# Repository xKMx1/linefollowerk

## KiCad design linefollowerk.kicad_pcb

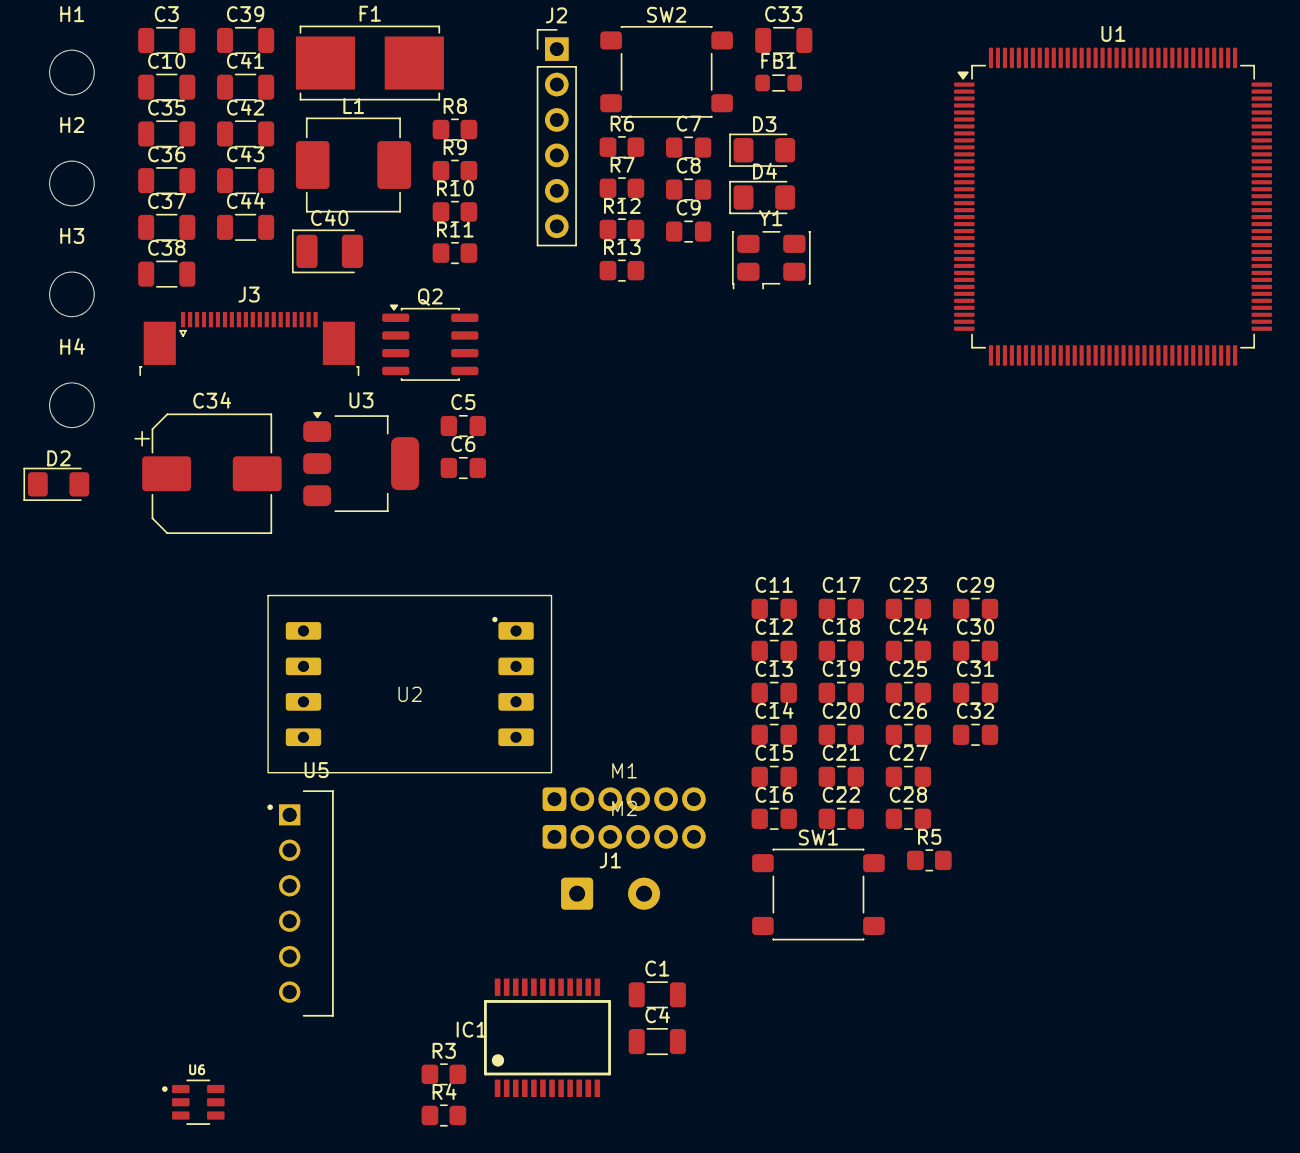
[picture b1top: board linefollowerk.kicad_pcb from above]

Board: 2 copper layers, 79 parts (0 on the bottom side), 57 nets, no tracks yet.

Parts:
C1, C4, C33, C37, C44: 100nF; C_1206_3216Metric
C3, C10, C35, C36, C39, C42, C43: 10uF; C_1206_3216Metric
C5, C23: 10uF; C_0805_2012Metric_Pad1.18x1.45mm_HandSolder
C6, C9, C11, C12, C13, C14, C15, C16, C17, C18, C19, C20, C21, C22, C24, C25, C29, C30: 100nF; C_0805_2012Metric_Pad1.18x1.45mm_HandSolder
C7, C8: 10pF; C_0805_2012Metric_Pad1.18x1.45mm_HandSolder
C26, C28: 1uF; C_0805_2012Metric_Pad1.18x1.45mm_HandSolder
C27: 10nF; C_0805_2012Metric_Pad1.18x1.45mm_HandSolder
C31, C32: 2.2uF; C_0805_2012Metric_Pad1.18x1.45mm_HandSolder
C34: 470uF; CP_Elec_8x10
C38, C41: 22uF; C_1206_3216Metric
C40: 22uF; CP_EIA-3528-21_Kemet-B_HandSolder
D2, D4: RED; LED_1206_3216Metric_Pad1.42x1.75mm_HandSolder
D3: GREEN; LED_1206_3216Metric_Pad1.42x1.75mm_HandSolder
F1: Fuse; Fuseholder_Littelfuse_Nano2_154x
FB1: 220Ω@100MHz; L_0805_2012Metric_Pad1.05x1.20mm_HandSolder
H1, H2, H3, H4: MountingHole; MountingHole_3.2mm_M3
IC1: TB6612FNG; SSOP24
J1: Conn_01x02_Pin; SolderWire-0.5sqmm_1x02_P4.8mm_D0.9mm_OD2.3mm
J2: SWD Connector; PinHeader_1x06_P2.54mm_Vertical
J3: FFC 20p; TE_2-1734839-0_1x20-1MP_P0.5mm_Horizontal
L1: 3.3uH; L_Vishay_IHLP-2525
M1, M2: POLOLU_ENCODER_FOOTPRINT
Q2: AO4407A; SOIC-8_3.9x4.9mm_P1.27mm
R3, R5, R9, R11: 10k; R_0805_2012Metric_Pad1.20x1.40mm_HandSolder
R4, R12, R13: 1k; R_0805_2012Metric_Pad1.20x1.40mm_HandSolder
R6, R10: 100k; R_0805_2012Metric_Pad1.20x1.40mm_HandSolder
R7: 47k; R_0805_2012Metric_Pad1.20x1.40mm_HandSolder
R8: 54.9k; R_0805_2012Metric_Pad1.20x1.40mm_HandSolder
SW1: PTS645; SW_SPST_PTS645Sx43SMTR92
SW2: SW_Push; SW_SPST_PTS645Sx43SMTR92
U1: STM32H743ZIT6; LQFP-144_20x20mm_P0.5mm
U2: MPU_6050
U3: AMS1117-3.3; SOT-223-3_TabPin2
U5: HC-06; MODULE_ZC142200
U6: TPS563201DDCR; SOT95P280X110-6N
Y1: Crystal_GND24; Crystal_SMD_5032-4Pin_5.0x3.2mm

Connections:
+3V3: C3.1, C4.1, C5.1, C6.1, C11.2, C12.2, C13.2, C14.2, C15.2, C16.2, C17.2, C18.2, C19.2, C20.2, C21.2, C22.2, C23.2, C24.2, C25.2, C28.2, C40.1, FB1.2, IC1.20 (VCC), J2.1, J3.1, M1.4 (VCC), M2.4 (VCC), R4.1, U1.6 (VBAT), U1.17 (VDD), U1.30 (VDD), U1.39 (VDD), U1.52 (VDD), U1.62 (VDD), U1.72 (VDD), U1.84 (VDD), U1.95 (VDD33_USB), U1.108 (VDD), U1.121 (VDD), U1.131 (VDD), U1.143 (PDR_ON), U1.144 (VDD), U3.2 (VO)
+3V3A: C26.2, C27.2, C30.1, FB1.1, U1.32 (VREF+), U1.33 (VDDA)
+5V: C38.2, C39.1, C41.2, L1.1, R8.1, U2.1 (VCC), U2.5 (VCC), U3.3 (VI), U5.5 (VCC)
/BOOT0: R5.1, U1.138 (BOOT0)
/NRST: C29.2, J2.5, U1.25 (NRST)
/OSC_IN: C7.2, U1.23 (PH0), Y1.1
/OSC_OUT: C8.1, U1.24 (PH1), Y1.3
/PA4: C33.1, R6.1, R7.2, U1.40 (PA4)
/Peripherials/LED_IN: D2.2 (A), R4.2
/Peripherials/MA_OUT1: IC1.1 (AO1), IC1.2 (AO1'), M1.6 (M1)
/Peripherials/MA_OUT2: IC1.5 (AO2), IC1.6 (AO2'), M1.5 (M2)
/Peripherials/MB_OUT1: IC1.11 (BO1), IC1.12 (BO1'), M2.6 (M1)
/Peripherials/MB_OUT2: IC1.7 (BO2), IC1.8 (BO2'), M2.5 (M2)
/Peripherials/PMOS_G: Q2.4 (G), R3.1
/START_SW: C9.1, SW2.1, U1.7 (PC13)
/SWCLK: J2.2, U1.109 (PA14)
/SWDIO: J2.4, U1.105 (PA13)
/SWO: J2.6, U1.133 (PB3)
A_IN1: IC1.21 (AIN1), U1.87 (PG2)
A_IN2: IC1.22 (AIN2), U1.88 (PG3)
A_PWM: IC1.23 (PWMA), U1.81 (PD12)
B_IN1: IC1.17 (BIN1), U1.89 (PG4)
B_IN2: IC1.16 (BIN2), U1.90 (PG5)
B_PWM: IC1.15 (PWMB), U1.82 (PD13)
GND: C1.2, C3.2, C4.2, C5.2, C6.2, C7.1, C8.2, C9.2, C10.2, C11.1, C12.1, C13.1, C14.1, C15.1, C16.1, C17.1, C18.1, C19.1, C20.1, C21.1, C22.1, C23.1, C24.1, C25.1, C26.1, C27.1, C28.1, C29.1, C30.2, C31.2, C32.1, C33.2, C34.2, C35.2, C36.2, C38.1, C39.2, C40.2, C41.1, C42.1, C43.1, C44.1, D2.1 (K), D3.1 (K), D4.1 (K), IC1.3 (PGND1), IC1.4 (PGND1'), IC1.9 (PGND2), IC1.10 (PGND2'), IC1.18 (GND), J1.1, J2.3, J3.20, M1.1 (GND), M2.1 (GND), R3.2, R5.2, R7.1, R9.1, R11.2, SW1.1, SW1.2, SW2.2, U1.16 (VSS), U1.31 (VSSA), U1.38 (VSS), U1.51 (VSS), U1.61 (VSS), U1.83 (VSS), U1.94 (VSS), U1.107 (VSS), U1.120 (VSS), U1.130 (VSS), U2.4 (GND), U2.8 (GND), U3.1 (GND), U5.4 (GND), U6.1 (GND), Y1.2 (G), Y1.4 (G)
HC_06_RX: U1.75 (PB14), U5.2 (RX)
HC_06_TX: U1.76 (PB15), U5.3 (TX)
L_E_OUT_A: M1.3 (OUT_A), U1.34 (PA0)
L_E_OUT_B: M1.2 (OUT_B), U1.35 (PA1)
MPU_RX: U1.119 (PD5), U2.2 (RX)
MPU_SCL: U1.136 (PB6), U2.6 (SCL)
MPU_SDA: U1.137 (PB7), U2.7 (SDA)
MPU_TX: U1.122 (PD6), U2.3 (TX)
M_STBY: IC1.19 (STBY), R11.1, U1.91 (PG6)
unnamed: C31.1, U1.106 (VCAP)
unnamed: C32.2, U1.71 (VCAP)
unnamed: D3.2 (A), R12.1
unnamed: D4.2 (A), R13.2
unnamed: F1.2, J1.2
unnamed: R12.2, U1.141 (PE0)
unnamed: R13.1, U1.142 (PE1)
unnamed: R10.2, U6.5 (EN)
unnamed: C37.2, L1.2, U6.2 (SW)
unnamed: C37.1, U6.6 (VBST)
unnamed: R8.2, R9.2, U6.4 (VFB)
R_E_OUT_A: M2.3 (OUT_A), U1.42 (PA6)
R_E_OUT_B: M2.2 (OUT_B), U1.43 (PA7)
SENS1: J3.9, U1.13 (PF3)
SENS2: J3.10, U1.14 (PF4)
SENS3: J3.11, U1.15 (PF5)
SENS4: J3.12, U1.18 (PF6)
SENS5: J3.8, U1.19 (PF7)
SENS6: J3.5, U1.20 (PF8)
SENS7: J3.6, U1.21 (PF9)
SENS8: J3.7, U1.22 (PF10)
VBAT: F1.1, Q2.5 (D), Q2.6 (D), Q2.7 (D), Q2.8 (D)
VIN: C1.1, C10.1, C34.1, C35.1, C36.1, C42.2, C43.2, C44.2, IC1.13 (VM2), IC1.14 (VM3), IC1.24 (VM1), Q2.1 (S), Q2.2 (S), Q2.3 (S), R6.2, R10.1, U6.3 (VIN)

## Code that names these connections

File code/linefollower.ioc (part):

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Mcu.Name=STM32H743ZITx
Mcu.Package=LQFP144
Mcu.UserName=STM32H743ZITx
PA0.Signal=S_TIM2_CH1_ETR
PA1.Signal=S_TIM2_CH2
PA13\ (JTMS/SWDIO).Mode=Trace_Asynchronous_SW
PA13\ (JTMS/SWDIO).Signal=DEBUG_JTMS-SWDIO
PA14\ (JTCK/SWCLK).Mode=Trace_Asynchronous_SW
PA14\ (JTCK/SWCLK).Signal=DEBUG_JTCK-SWCLK
PA4.Signal=ADCx_INP18
PA6.Signal=S_TIM3_CH1
PA7.Signal=S_TIM3_CH2
PB14.Mode=Asynchronous
PB14.Signal=USART1_TX
PB15.Mode=Asynchronous
PB15.Signal=USART1_RX
PB3\ (JTDO/TRACESWO).Mode=Trace_Asynchronous_SW
PB3\ (JTDO/TRACESWO).Signal=DEBUG_JTDO-SWO
PB6.Mode=I2C
PB6.Signal=I2C1_SCL
PB7.Mode=I2C
PB7.Signal=I2C1_SDA
PC13.GPIOParameters=GPIO_PuPd,GPIO_Label,GPIO_ModeDefaultEXTI
PC13.GPIO_Label=BTN_START
PC13.GPIO_ModeDefaultEXTI=GPIO_MODE_IT_FALLING
PC13.GPIO_PuPd=GPIO_PULLUP
PC13.Signal=GPXTI13
PD12.Signal=S_TIM4_CH1
PD13.Signal=S_TIM4_CH2
PE0.GPIOParameters=GPIO_Label
PE0.GPIO_Label=LED1
PE0.Signal=GPIO_Output
PE1.GPIOParameters=GPIO_Label
PE1.GPIO_Label=LED2
PE1.Signal=GPIO_Output
PF10.Mode=IN6-Single-Ended
PF10.Signal=ADC3_INP6
PF3.Mode=IN5-Single-Ended
PF3.Signal=ADC3_INP5
PF4.Mode=IN9-Single-Ended
PF4.Signal=ADC3_INP9
PF5.Mode=IN4-Single-Ended
PF5.Signal=ADC3_INP4
PF6.Mode=IN8-Single-Ended
PF6.Signal=ADC3_INP8
PF7.Mode=IN3-Single-Ended
PF7.Signal=ADC3_INP3
PF8.Mode=IN7-Single-Ended
PF8.Signal=ADC3_INP7
PF9.Mode=IN2-Single-Ended
PF9.Signal=ADC3_INP2
PG2.GPIOParameters=GPIO_Label
PG2.GPIO_Label=AIN1
PG2.Signal=GPIO_Output
PG3.GPIOParameters=GPIO_Label
PG3.GPIO_Label=AIN2
PG3.Signal=GPIO_Output
PG4.GPIOParameters=GPIO_Label
PG4.GPIO_Label=BIN1
PG4.Signal=GPIO_Output
PG5.GPIOParameters=GPIO_Label
PG5.GPIO_Label=BIN2
PG5.Signal=GPIO_Output
PG6.GPIOParameters=GPIO_Label
PG6.GPIO_Label=M_STBY
PG6.Signal=GPIO_Output
PH0-OSC_IN\ (PH0).Mode=HSE-External-Oscillator
PH0-OSC_IN\ (PH0).Signal=RCC_OSC_IN
PH1-OSC_OUT\ (PH1).Mode=HSE-External-Oscillator
PH1-OSC_OUT\ (PH1).Signal=RCC_OSC_OUT
RCC.HSE_VALUE=25000000
RCC.SYSCLKFreq_VALUE=480000000
RCC.SYSCLKSource=RCC_SYSCLKSOURCE_PLLCLK
board=custom
